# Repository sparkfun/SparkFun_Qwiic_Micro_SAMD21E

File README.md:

SparkFun Qwiic Micro - SAMD21E
========================================

[*SparkFun Qwiic Micro - SAMD21E (DEV-15423)*](https://www.sparkfun.com/products/15423)

Looking for a super small microcontroller to use with the [Qwiic eco-system](https://www.sparkfun.com/qwiic)? The SparkFun Qwiic Micro is molded to fit our standard 1"x1" Qwiic standard size which makes it one of our smallest micro-controller offerings to date. At it's core is the powerful and versatile ATSAMD21E18, which is an ARM Cortex M0+, 32-bit microcontroller, with 256KB of flash memory that can run at up to 48MHz! It has 12 digital pins which include 5 analog pins, SPI, I²C, and an additional UART data bus as well as a Qwiic connector for easy integration into the Qwiic ecosystem and I²C prototyping.

On the underside of the Qwiic Micro, we've left open pads for a LiPo Battery connector that you can add yourself, if you wish you can make the micro-controller portable. We've also provided pads on the underside for a flash memory chip to maximize the board's memory capacity. The SparkFun Qwiic Micro comes programmed with a UF2 Bootloader making it easy to program with easy driver installation! If you need a tiny but mighty micro-controller for you next project check out the SparkFun Qwiic Micro.

Repository Contents
-------------------

* **/Documentation** - Data sheets, additional product information
* **/Hardware** - Eagle design files (.brd, .sch)
* **/Firmware** - UF2 Bootloader and Arduino Board Files
* **/Production** - Production panel files (.brd)

Documentation
--------------
* **[Hookup Guide](https://learn.sparkfun.com/tutorials/sparkfun-qwiic-micro-samd21e-hookup-guide)** - Basic hookup guide for the Qwiic Micro
* **[Graphical Datasheet](https://github.com/sparkfun/Graphical_Datasheets)** - Graphical datasheet for Qwiic Micro can be found in this repo
* **[Qwiic Ecosystem](https://www.sparkfun.com/qwiic)** - Qwiic enabled for fast prototyping!

License Information
-------------------

This product is _**open source**_! 

Please review the LICENSE.md file for license information. 

If you have any questions or concerns on licensing, please contact technical support on our [SparkFun forums](https://forum.sparkfun.com/viewforum.php?f=152).

Distributed as-is; no warranty is given.

- Your friends at SparkFun.

_<COLLABORATION CREDIT>_

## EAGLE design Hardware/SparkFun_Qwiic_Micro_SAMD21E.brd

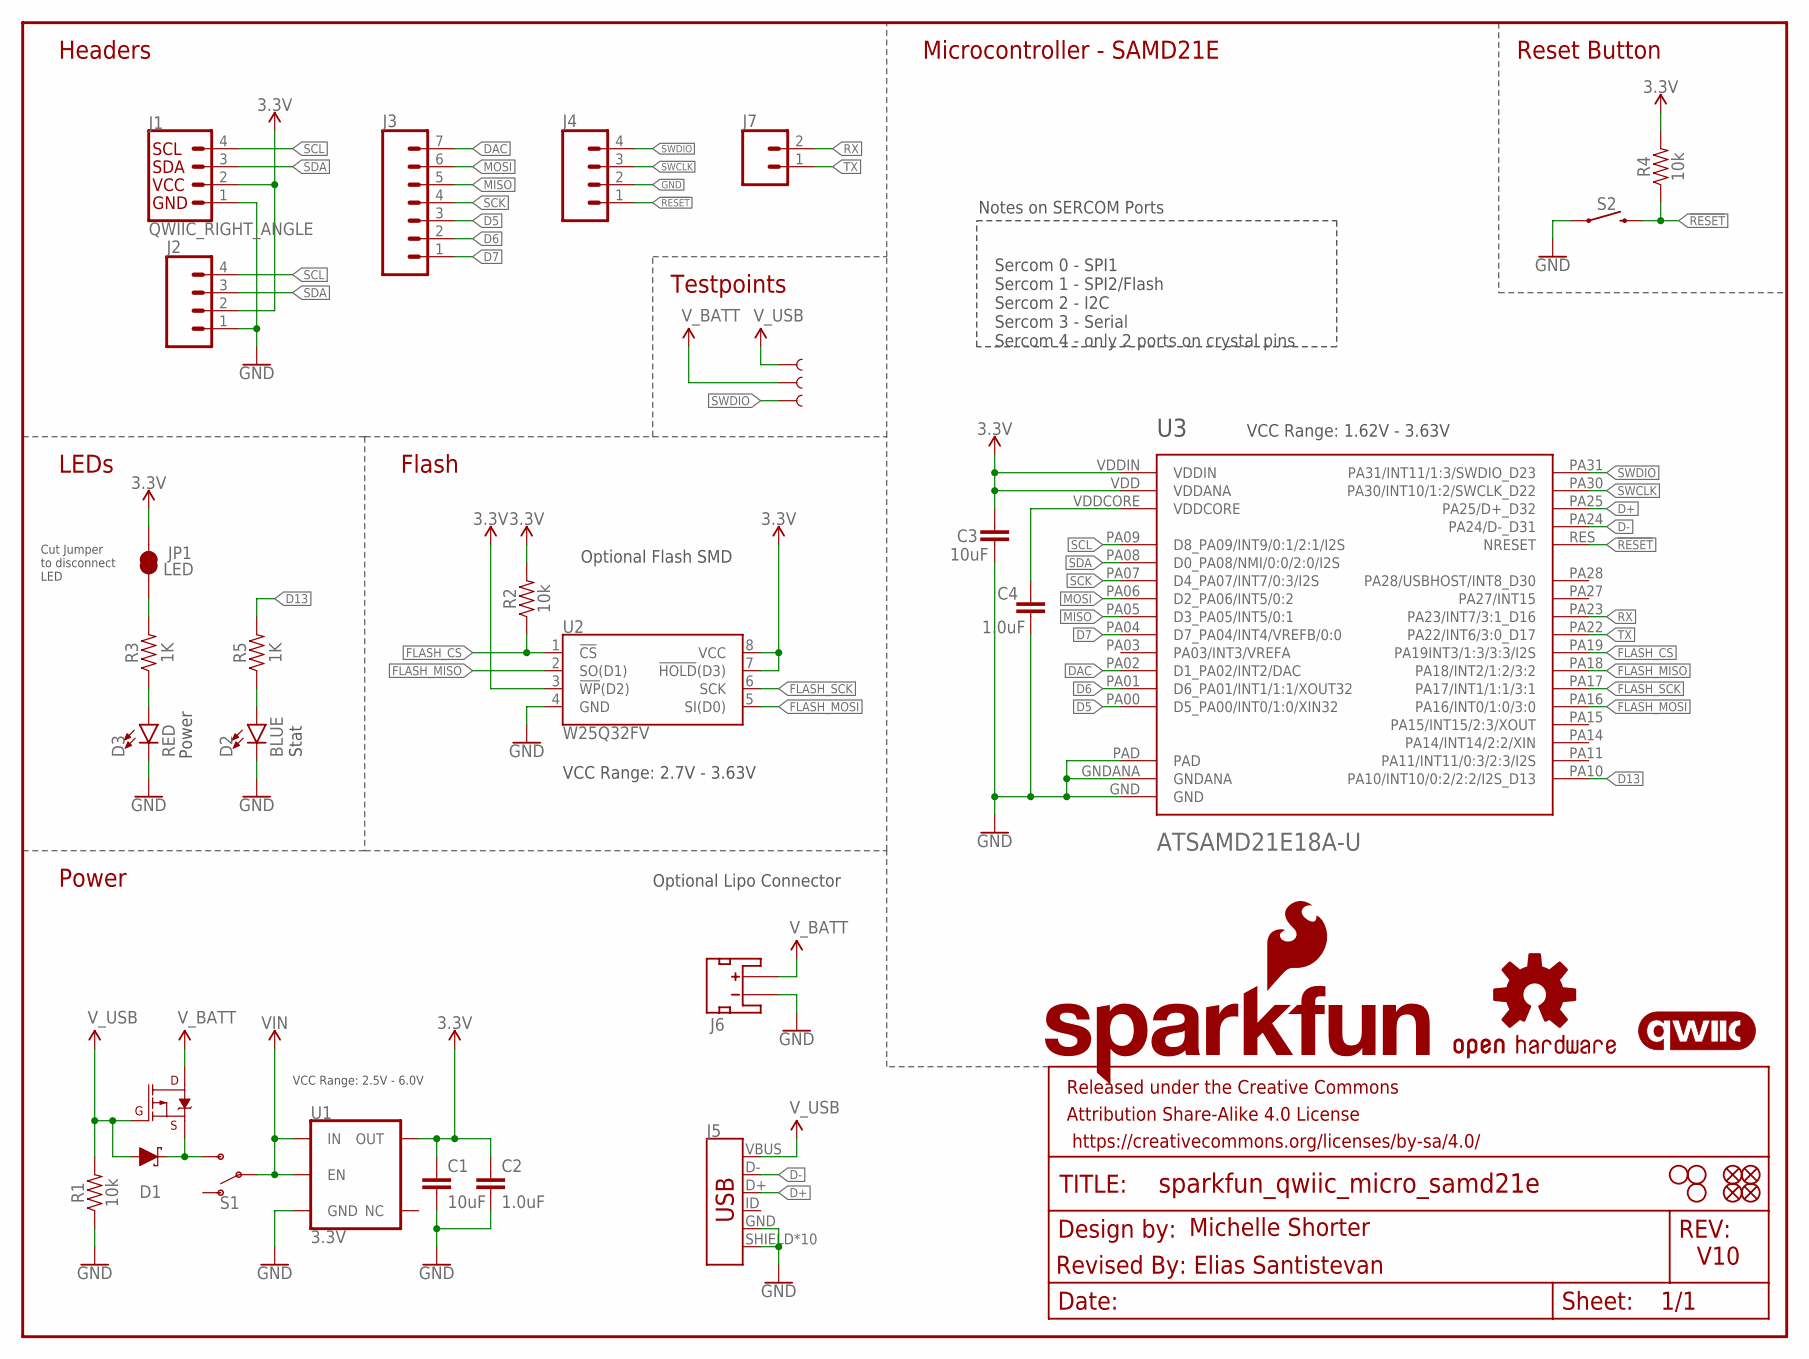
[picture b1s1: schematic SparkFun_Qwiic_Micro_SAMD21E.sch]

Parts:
C1, C3: 10uF; 0603
C2, C4: 1.0uF; 0402
D1: 1A/23V/620mV; SOD-323
D2: BLUE; LED-0603
D3: RED; LED-0603
FD1, FD2, FD3, FD4: FIDUCIALUFIDUCIAL; FIDUCIAL-MICRO
FRAME1: FRAME-LETTER; CREATIVE_COMMONS
H1, H2, H3: STAND-OFF
J1: QWIIC_RIGHT_ANGLE; JST04_1MM_RA
J2: CONN_041X04_NO_SILK; 1X04_NO_SILK
J3: CONN_07NO_SILK; 1X07_NO_SILK
J4: CONN_041.27MM_NO_SILK; 1X04_1.27MM_NO_SILK
J5: USB_MICRO-B_HALF_PTH_MILL; USB-MICROB-PTH-MILL
J6: JST_2MM_MALE; JST-2-SMD
J7: CONN_021X02_NO_SILK; 1X02_NO_SILK
JP1: LED; SMT-JUMPER_2_NC_TRACE_SILK
LOGO1: SFE_LOGO_NAME.1_INCH; SFE_LOGO_NAME_.1
LOGO2: SFE_LOGO_FLAME.2_INCH; SFE_LOGO_FLAME_.2
LOGO3: OSHW-LOGOS; OSHW-LOGO-S
LOGO4: QWIIC_LOGO_3MM; QWIIC_3MM
Q1: 3.1A/30V/105mΩ; SOT23-3
R1, R2, R4: 10k; 0402
R3, R5: 1K; 0402
S1: SWITCH-SPDT-SMD-RIGHT-ANGLE; SWITCH_SPST_SMD_A
S2: MOMENTARY-SWITCH-SPST-SMD-4.6X2.8MM; TACTILE_SWITCH_SMD_4.6X2.8MM
TP1, TP2, TP3: TEST-POINTTP_15TH_THRU; TP_15TH
U1: 3.3V; SOT23-5
U2: W25Q32FV; SOIC-8
U3: ATSAMD21E18A-U; QFN-32_SAMD

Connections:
3.3V: C1.1, C2.1, C3.1, J1.2, J2.2, JP1.2, R2.2, R4.2, U1.5 (OUT), U2.3 (!WP!(D2)), U2.7 (!HOLD!(D3)), U2.8 (VCC), U3.VDD (VDDANA), U3.VDDIN
!RESET: J4.1, R4.1, S2.3 (2), S2.4 (2), U3.RES (NRESET)
D5: J3.3, U3.PA00 (D5_PA00/INT0/1:0/XIN32)
D6: J3.2, U3.PA01 (D6_PA01/INT1/1:1/XOUT32)
D7: J3.1, U3.PA04 (D7_PA04/INT4/VREFB/0:0)
D13: R5.2, U3.PA10 (PA10/INT10/0:2/2:2/I2S_D13)
D+: J5.D+, U3.PA25 (PA25/D+_D32)
D-: J5.D-, U3.PA24 (PA24/D-_D31)
DAC: J3.7, U3.PA02 (D1_PA02/INT2/DAC)
FLASH_CS: R2.1, U2.1 (!CS!), U3.PA19 (PA19INT3/1:3/3:3/I2S)
FLASH_MISO: U2.2 (SO(D1)), U3.PA18 (PA18/INT2/1:2/3:2)
FLASH_MOSI: U2.5 (SI(D0)), U3.PA16 (PA16/INT0/1:0/3:0)
FLASH_SCK: U2.6 (SCK), U3.PA17 (PA17/INT1/1:1/3:1)
GND: C1.2, C2.2, C3.2, C4.1, D2.C, D3.C, J1.1, J2.1, J4.2, J5.GND, J5.SHIELD, J5.SHIELD2 (SHIELD), J5.SHIELD3 (SHIELD), J5.SHIELD4 (SHIELD), J5.SHIELD5 (SHIELD), J5.SHIELD6 (SHIELD), J5.SHIELD7 (SHIELD), J5.SHIELD8 (SHIELD), J5.SHIELD9 (SHIELD), J5.SHIELD10 (SHIELD), J6.1 (-), R1.1, S2.1, S2.2 (1), U1.2 (GND), U2.4 (GND), U3.GND, U3.GNDANA, U3.PAD
MISO: J3.5, U3.PA05 (D3_PA05/INT5/0:1)
MOSI: J3.6, U3.PA06 (D2_PA06/INT5/0:2)
unnamed: D3.A, R3.1
unnamed: JP1.1, R3.2
unnamed: D2.A, R5.1
RX: J7.2, U3.PA23 (PA23/INT7/3:1_D16)
SCK: J3.4, U3.PA07 (D4_PA07/INT7/0:3/I2S)
SCL: J1.4, J2.4, U3.PA09 (D8_PA09/INT9/0:1/2:1/I2S)
SDA: J1.3, J2.3, U3.PA08 (D0_PA08/NMI/0:0/2:0/I2S)
SWCLK: J4.3, U3.PA30 (PA30/INT10/1:2/SWCLK_D22)
SWDIO: J4.4, TP3.P$1, U3.PA31 (PA31/INT11/1:3/SWDIO_D23)
TX: J7.1, U3.PA22 (PA22/INT6/3:0_D17)
VDDCORE: C4.2, U3.VDDCORE
VIN: S1.2, U1.1 (IN), U1.3 (EN)
VIN1: D1.C, Q1.2 (S), S1.3 (S)
V_BATT: J6.2 (+), Q1.3 (D), TP2.P$1
V_USB: D1.A, J5.VBUS, Q1.1 (G), R1.2, TP1.P$1

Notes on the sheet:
Sercom 0 - SPI1 Sercom 1 - SPI2/Flash Sercom 2 - I2C Sercom 3 - Serial Sercom 4 - only 2 ports on crystal pins
Headers
LEDs
Power
Microcontroller - SAMD21E
Optional Flash SMD
V10
Michelle Shorter
Revised By: Elias Santistevan
Testpoints
Reset Button
Flash
Cut Jumper to disconnect LED
Notes on SERCOM Ports
Stat
VCC Range: 2.5V - 6.0V
VCC Range: 1.62V - 3.63V
VCC Range: 2.7V - 3.63V
Optional Lipo Connector

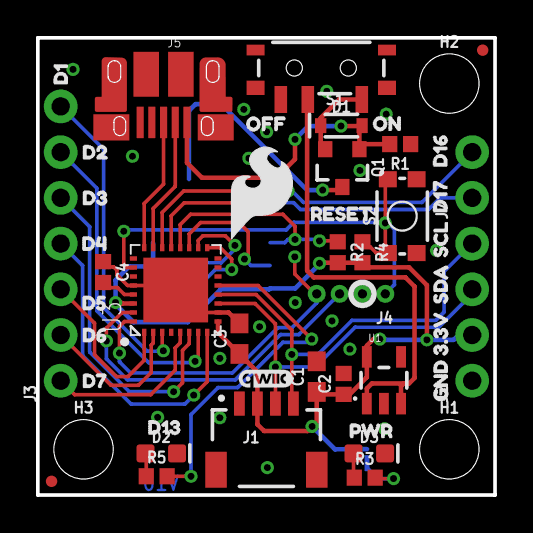
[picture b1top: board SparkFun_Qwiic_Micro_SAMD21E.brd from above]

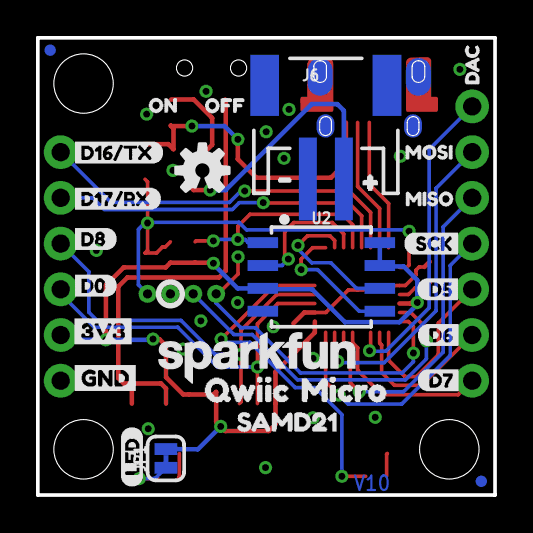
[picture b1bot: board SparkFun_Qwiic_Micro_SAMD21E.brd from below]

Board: 2 copper layers, 25.4 x 25.4 mm, 80 parts (28 on the bottom side), 31 nets.

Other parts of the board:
U$1: D00
U$2: GND-03
U$3: #23
U$4: #24
U$5: 3#3V10
U$6: D12
U$7: D166
U$8: D177
U$9: D16#TX4
U$10: QWIIC2
U$11: D17#RX3
U$12: D75
U$13: DAC1
U$14: MISO0
U$15: SAMD213
U$16: MOSI2
U$17: 3V3-03
U$18, U$46: ON12
U$19, U$45: OFF13
U$20: SCK7
U$21: RESET0
U$22: D85
U$23: MICRO2
U$24: LED1
U$25: D50
U$26: D61
U$27: D72
U$28: D21
U$29: D136
U$36: D33
U$37: D41
U$38: D52
U$39: D65
U$44: GND11
U$47: PWR16
U$49: SCL8
U$50: SDA9

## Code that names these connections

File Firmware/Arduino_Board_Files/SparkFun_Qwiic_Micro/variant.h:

/*
  Copyright (c) 2014-2015 Arduino LLC.  All right reserved.

  This library is free software; you can redistribute it and/or
  modify it under the terms of the GNU Lesser General Public
  License as published by the Free Software Foundation; either
  version 2.1 of the License, or (at your option) any later version.

  This library is distributed in the hope that it will be useful,
  but WITHOUT ANY WARRANTY; without even the implied warranty of
  MERCHANTABILITY or FITNESS FOR A PARTICULAR PURPOSE.
  See the GNU Lesser General Public License for more details.

  You should have received a copy of the GNU Lesser General Public
  License along with this library; if not, write to the Free Software
  Foundation, Inc., 51 Franklin St, Fifth Floor, Boston, MA  02110-1301  USA
*/

#ifndef _VARIANT_ARDUINO_ZERO_
#define _VARIANT_ARDUINO_ZERO_

// The definitions here needs a SAMD core >=1.6.6
#define ARDUINO_SAMD_VARIANT_COMPLIANCE 10606

/*----------------------------------------------------------------------------
 *        Definitions
 *----------------------------------------------------------------------------*/

/** Frequency of the board main oscillator */
#define VARIANT_MAINOSC		(32768ul)

/** Master clock frequency */
#define VARIANT_MCK			  (F_CPU)

/*----------------------------------------------------------------------------
 *        Headers
 *----------------------------------------------------------------------------*/

#include "WVariant.h"

#ifdef __cplusplus
#include "SERCOM.h"
#include "Uart.h"
#endif // __cplusplus

#ifdef __cplusplus
extern "C"
{
#endif // __cplusplus

/*----------------------------------------------------------------------------
 *        Pins
 *----------------------------------------------------------------------------*/

// Number of pins defined in PinDescription array
#define PINS_COUNT           (36u)
#define NUM_DIGITAL_PINS     (30u)
#define NUM_ANALOG_INPUTS    (6u)
#define NUM_ANALOG_OUTPUTS   (1u)
#define analogInputToDigitalPin(p)  ((p < 6u) ? (p) + 22u : -1)

#define digitalPinToPort(P)        ( &(PORT->Group[g_APinDescription[P].ulPort]) )
#define digitalPinToBitMask(P)     ( 1 << g_APinDescription[P].ulPin )
//#define analogInPinToBit(P)        ( )
#define portOutputRegister(port)   ( &(port->OUT.reg) )
#define portInputRegister(port)    ( &(port->IN.reg) )
#define portModeRegister(port)     ( &(port->DIR.reg) )
#define digitalPinHasPWM(P)        ( g_APinDescription[P].ulPWMChannel != NOT_ON_PWM || g_APinDescription[P].ulTCChannel != NOT_ON_TIMER )

/*
 * digitalPinToTimer(..) is AVR-specific and is not defined for SAMD
 * architecture. If you need to check if a pin supports PWM you must
 * use digitalPinHasPWM(..).
 *
 * https://github.com/arduino/Arduino/issues/1833
 */
// #define digitalPinToTimer(P)

// RX and TX LEDs are not present on the board. 
#define PIN_LED_13           (13u)
#define PIN_LED_RXL          (25u)
#define PIN_LED_TXL          (26u)
#define PIN_LED              PIN_LED_13
#define PIN_LED2             PIN_LED_RXL
#define PIN_LED3             PIN_LED_TXL
#define LED_BUILTIN          PIN_LED_13

/*
 * Analog pins
 */
#define PIN_A0               (24u)
#define PIN_A1               (PIN_A0+1)
#define PIN_A2               (PIN_A0+2)
#define PIN_A3               (PIN_A0+3)
#define PIN_A4               (PIN_A0+4)
#define PIN_A5               (PIN_A0+5)
#define PIN_DAC0             PIN_A0

static const uint8_t A0  = PIN_A0;
static const uint8_t A1  = PIN_A1;
static const uint8_t A2  = PIN_A2;
static const uint8_t A3  = PIN_A3;
static const uint8_t A4  = PIN_A4;
static const uint8_t A5  = PIN_A5;
static const uint8_t DAC0 = PIN_DAC0;
#define ADC_RESOLUTION		12

/*
 * Serial interfaces
 */

// Serial
#define PIN_SERIAL_TX       (16ul)
#define PIN_SERIAL_RX       (17ul)
#define PAD_SERIAL_TX       (UART_TX_PAD_0)
#define PAD_SERIAL_RX       (SERCOM_RX_PAD_1)

/*
 * SPI Interfaces
 */
#define SPI_INTERFACES_COUNT 2

#define PIN_SPI_MOSI         (2u)
#define PIN_SPI_MISO         (3u)
#define PIN_SPI_SCK          (4u)
#define PIN_SPI_SS			     (5u)
#define PERIPH_SPI           sercom0
#define PAD_SPI_TX           SPI_PAD_2_SCK_3
#define PAD_SPI_RX           SERCOM_RX_PAD_1

static const uint8_t SS	  = PIN_SPI_SS ;	// SERCOM0 last PAD is present on D6 but HW SS isn't used. Set here only for reference.
static const uint8_t MOSI = PIN_SPI_MOSI ;
static const uint8_t MISO = PIN_SPI_MISO ;
static const uint8_t SCK  = PIN_SPI_SCK ;

#define PIN_SPI1_MOSI         (18u)
#define PIN_SPI1_SCK          (19u)
#define PIN_SPI1_MISO         (20u)
#define PIN_SPI1_SS		        (21u)
#define PERIPH_SPI1           sercom1
#define PAD_SPI1_TX           SPI_PAD_0_SCK_1
#define PAD_SPI1_RX           SERCOM_RX_PAD_2

static const uint8_t FLASH_SS   = PIN_SPI1_SS ;	
static const uint8_t FLASH_MOSI = PIN_SPI1_MOSI ;
static const uint8_t FLASH_MISO = PIN_SPI1_MISO ;
static const uint8_t FLASH_SCK  = PIN_SPI1_SCK ;

/*
 * Wire Interfaces
 */
//I2C/Qwiic Interface
#define WIRE_INTERFACES_COUNT 1

#define PIN_WIRE_SDA         (9u)
#define PIN_WIRE_SCL         (10u)
#define PERIPH_WIRE          sercom2
#define WIRE_IT_HANDLER      SERCOM2_Handler

static const uint8_t SDA = PIN_WIRE_SDA;
static const uint8_t SCL = PIN_WIRE_SCL;

/*
 * USB
 */
#define PIN_USB_HOST_ENABLE (30ul)
#define PIN_USB_DM          (31ul)
#define PIN_USB_DP          (32ul)


#ifdef __cplusplus
}
#endif

/*----------------------------------------------------------------------------
 *        Arduino objects - C++ only
 *----------------------------------------------------------------------------*/

#ifdef __cplusplus

/*	=========================
 *	===== SERCOM DEFINITION
 *	=========================
*/
extern SERCOM sercom0;
extern SERCOM sercom1;
extern SERCOM sercom2;
extern SERCOM sercom3;


extern Uart Serial;


#endif

// These serial port names are intended to allow libraries and architecture-neutral
// sketches to automatically default to the correct port name for a particular type
// of use.  For example, a GPS module would normally connect to SERIAL_PORT_HARDWARE_OPEN,
// the first hardware serial port whose RX/TX pins are not dedicated to another use.
//
// SERIAL_PORT_MONITOR        Port which normally prints to the Arduino Serial Monitor
//
// SERIAL_PORT_USBVIRTUAL     Port which is USB virtual serial
//
// SERIAL_PORT_LINUXBRIDGE    Port which connects to a Linux system via Bridge library
//
// SERIAL_PORT_HARDWARE       Hardware serial port, physical RX & TX pins.
//
// SERIAL_PORT_HARDWARE_OPEN  Hardware serial ports which are open for use.  Their RX & TX
//                            pins are NOT connected to anything by default.
#define SERIAL_PORT_USBVIRTUAL      SerialUSB
#define SERIAL_PORT_MONITOR         SerialUSB
#define SERIAL_PORT_HARDWARE        Serial
#define SERIAL_PORT_HARDWARE_OPEN   Serial

#endif /* _VARIANT_ARDUINO_ZERO_ */

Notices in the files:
parts and their libraries:
SparkFun-Connectors: Licensing: Creative Commons ShareAlike 4.0 International - https://creativecommons.org/licenses/by-sa/4.0
SparkFun-Aesthetics: Released under the Creative Commons Attribution Share-Alike 4.0 License
SparkFun-Aesthetics: https://creativecommons.org/licenses/by-sa/4.0
